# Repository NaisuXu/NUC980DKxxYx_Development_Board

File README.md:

# NUC980DKxxYx_Development_Board

## Introduction

This is a development board project for Nuvoton NUC980 Series. It can be used for LQFP128 package chips such as NUC980DK61YC, NUC980DK71YC.

This project is designed with [Kicad](https://www.kicad.org/).

## 3D Views

## What is the NUC980

> The NUC980 series with the ARM926EJ-S core can operate at up to 300 MHz . It offers 64-pin, 128-pin and 216-pin LQFP packages stacked with 64 MB and 128 MB DDR-II Memory to reduce PCB size and EMI issues. Rich peripherals include 10 sets of UART , dual Ethernet, 4 sets CAN 2.0B, dual SDIO / eMMC interface, NAND Flash interface, QSPI NAND, 8 Ports USB Host, ISO-7816 interface and High-Speed USB 2.0 host / device controller to allow more flexibility in designs. The NUC980 also integrates the crypto engine which provides hardware acceleration for AES, SHA, ECC, RSA  function.
>
> It supports industrial temperature from - 40 ℃  to 85 ℃  and targets Industrial Control, Industrial IoT Gateway, Network Printer, Meter Concentrator and Smart Home Gateway applications.

For more details see the Nuvoton website: [NUC980 工业控制物联网系列](https://www.nuvoton.com.cn/products/microprocessors/arm9-mpus/nuc980-industrial-control-iot-series/)

## License
<br />This work is licensed under a <a rel="license" href="http://creativecommons.org/licenses/by-sa/4.0/">Creative Commons Attribution-ShareAlike 4.0 International License</a>.

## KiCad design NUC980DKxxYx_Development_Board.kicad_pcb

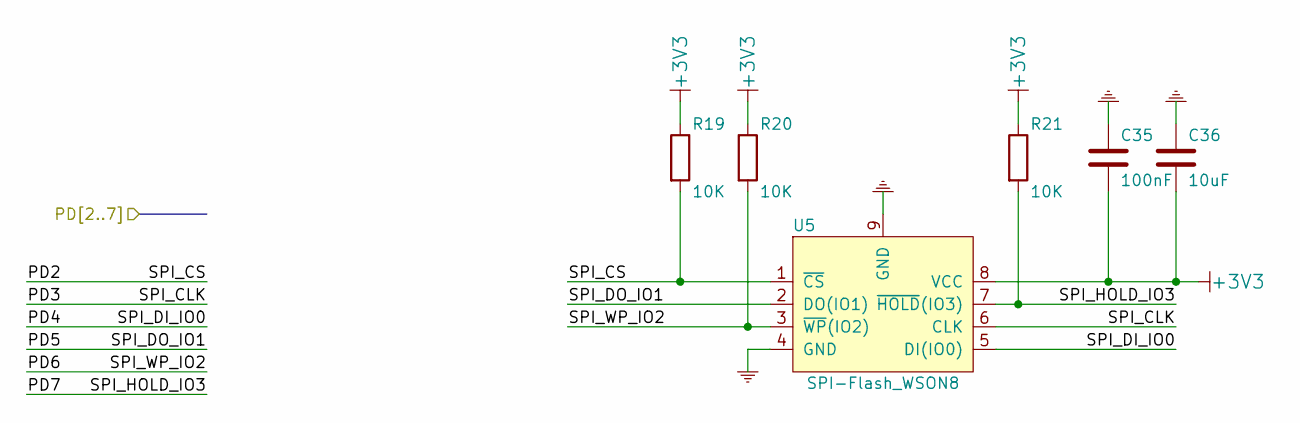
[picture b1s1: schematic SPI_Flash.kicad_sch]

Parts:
C35: 100nF; C_0603_1608Metric
C36: 10uF; C_0805_2012Metric
R19, R20, R21: 10K; R_0603_1608Metric
U5: SPI-Flash_WSON8; WSON-8-1EP_8x6mm_P1.27mm_EP3.4x4.3mm

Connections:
+3V3: C35.2, C36.2, R19.1, R20.1, R21.1, U5.8 (VCC); also elsewhere on the board
/PD2: R19.2, U5.1 (~CS); also elsewhere on the board
/PD3: U5.6 (CLK); also elsewhere on the board
/PD4: U5.5 (DI(IO0)); also elsewhere on the board
/PD5: U5.2 (DO(IO1)); also elsewhere on the board
/PD6: R20.2, U5.3 (~WP(IO2)); also elsewhere on the board
/PD7: R21.2, U5.7 (~HOLD(IO3)); also elsewhere on the board
GND: C35.1, C36.1, U5.4 (GND), U5.9 (GND); also elsewhere on the board

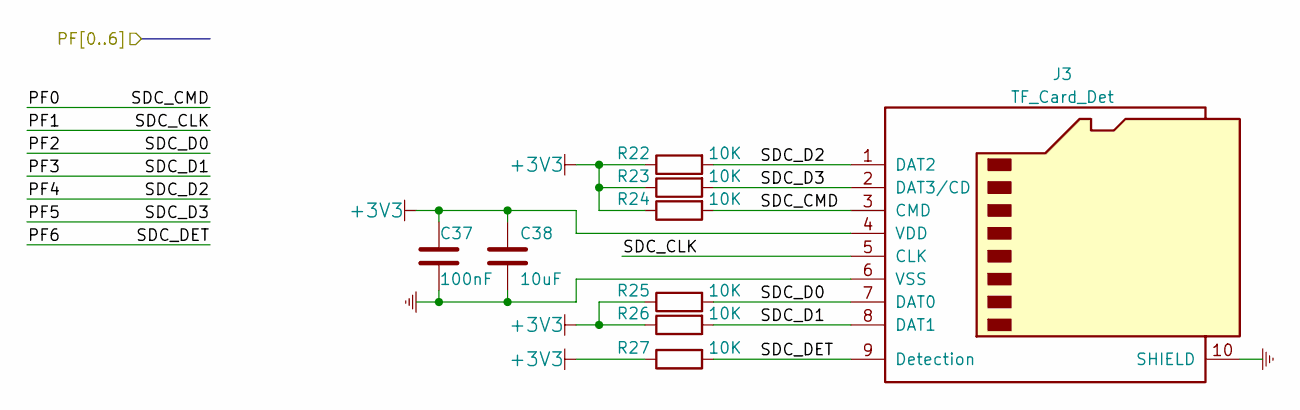
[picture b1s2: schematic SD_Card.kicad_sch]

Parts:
C37: 100nF; C_0603_1608Metric
C38: 10uF; C_0805_2012Metric
J3: TF_Card_Det; microSD_Push-Push_9P_4Pad
R22, R23, R24, R25, R26, R27: 10K; R_0603_1608Metric

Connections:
+3V3: C37.1, C38.1, J3.4 (VDD), R22.1, R23.1, R24.1, R25.1, R26.1, R27.1; also elsewhere on the board
/PF0: J3.3 (CMD), R24.2; also elsewhere on the board
/PF1: J3.5 (CLK); also elsewhere on the board
/PF2: J3.7 (DAT0), R25.2; also elsewhere on the board
/PF3: J3.8 (DAT1), R26.2; also elsewhere on the board
/PF4: J3.1 (DAT2), R22.2; also elsewhere on the board
/PF5: J3.2 (DAT3/CD), R23.2; also elsewhere on the board
/PF6: J3.9 (Detection), R27.2; also elsewhere on the board
GND: C37.2, C38.2, J3.6 (VSS), J3.10 (SHIELD); also elsewhere on the board

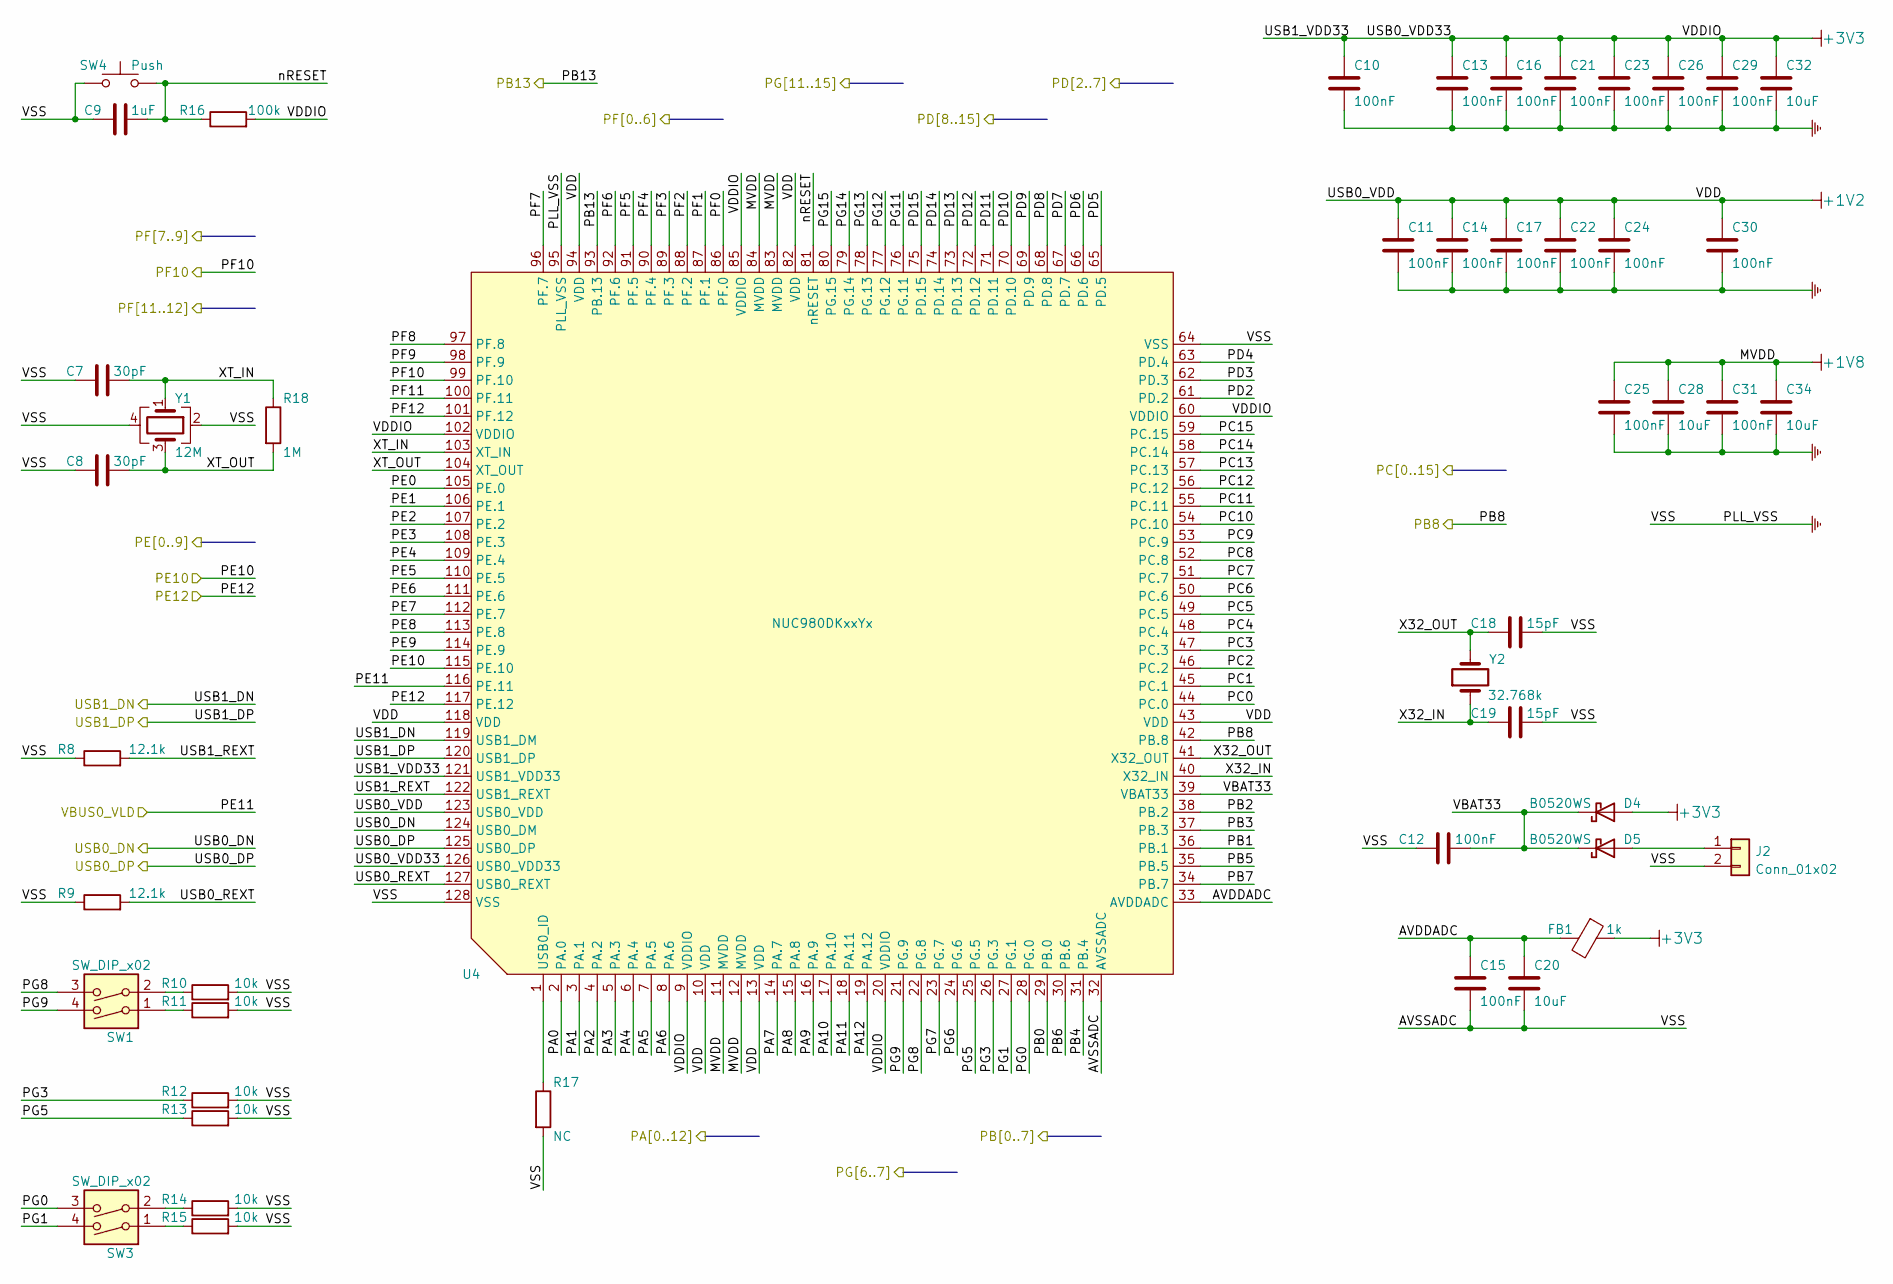
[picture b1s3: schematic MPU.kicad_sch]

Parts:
C7, C8: 30pF; C_0603_1608Metric
C9: 1uF; C_0603_1608Metric
C10, C11, C12, C13, C14, C15, C16, C17, C21, C22, C23, C24, C25, C26, C29, C30, C31: 100nF; C_0603_1608Metric
C18, C19: 15pF; C_0603_1608Metric
C20, C28, C32, C34: 10uF; C_0805_2012Metric
D4, D5: B0520WS; D_SOD-323
FB1: 1k; L_0603_1608Metric
J2: Conn_01x02; PinHeader_1x02_P2.54mm_Vertical
R8, R9: 12.1k; R_0603_1608Metric
R10, R11, R12, R13, R14, R15: 10k; R_0603_1608Metric
R16: 100k; R_0603_1608Metric
R17: NC; R_0603_1608Metric
R18: 1M; R_0603_1608Metric
SW1, SW3: SW_DIP_x02; SW_DIP_SPSTx02_Slide_9.78x7.26mm_W7.62mm_P2.54mm
SW4: Push; SW_SPST_CK_RS282G05A3
U4: NUC980DKxxYx; LQFP-128_14x14mm_P0.4mm
Y1: 12M; Crystal_SMD_3225-4Pin_3.2x2.5mm
Y2: 32.768k; Crystal_SMD_3215-2Pin_3.2x1.5mm

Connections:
+1V2: C11.1, C14.1, C17.1, C22.1, C24.1, C30.1, U4.10 (VDD), U4.13 (VDD), U4.43 (VDD), U4.82 (VDD), U4.94 (VDD), U4.118 (VDD), U4.123 (USB0_VDD); also elsewhere on the board
+1V8: C25.1, C28.1, C31.1, C34.1, U4.11 (MVDD), U4.12 (MVDD), U4.83 (MVDD), U4.84 (MVDD); also elsewhere on the board
+3V3: C10.1, C13.1, C16.1, C21.1, C23.1, C26.1, C29.1, C32.1, D4.2 (A), FB1.1, R16.2, U4.9 (VDDIO), U4.20 (VDDIO), U4.60 (VDDIO), U4.85 (VDDIO), U4.102 (VDDIO), U4.121 (USB1_VDD33), U4.126 (USB0_VDD33); also elsewhere on the board
/MPU/AVDDADC: C15.1, C20.1, FB1.2, U4.33 (AVDDADC)
/MPU/PG0: SW3.3, U4.28 (PG.0)
/MPU/PG1: SW3.4, U4.27 (PG.1)
/MPU/PG3: R12.1, U4.26 (PG.3)
/MPU/PG5: R13.1, U4.25 (PG.5)
/MPU/PG8: SW1.3, U4.22 (PG.8)
/MPU/PG9: SW1.4, U4.21 (PG.9)
/MPU/USB0_REXT: R9.2, U4.127 (USB0_REXT)
/MPU/USB1_REXT: R8.2, U4.122 (USB1_REXT)
/MPU/VBAT33: C12.2, D4.1 (K), D5.1 (K), U4.39 (VBAT33)
/MPU/X32_IN: C19.1, U4.40 (X32_IN), Y2.1
/MPU/X32_OUT: C18.1, U4.41 (X32_OUT), Y2.2
/MPU/XT_IN: C7.2, R18.1, U4.103 (XT_IN), Y1.1
/MPU/XT_OUT: C8.2, R18.2, U4.104 (XT_OUT), Y1.3
/MPU/nRESET: C9.2, R16.1, SW4.1, U4.81 (nRESET)
/PA0: U4.2 (PA.0); also elsewhere on the board
/PA1: U4.3 (PA.1); also elsewhere on the board
/PA2: U4.4 (PA.2); also elsewhere on the board
/PA3: U4.5 (PA.3); also elsewhere on the board
/PA4: U4.6 (PA.4); also elsewhere on the board
/PA5: U4.7 (PA.5); also elsewhere on the board
/PA6: U4.8 (PA.6); also elsewhere on the board
/PA7: U4.14 (PA.7); also elsewhere on the board
/PA8: U4.15 (PA.8); also elsewhere on the board
/PA9: U4.16 (PA.9); also elsewhere on the board
/PA10: U4.17 (PA.10); also elsewhere on the board
/PA11: U4.18 (PA.11); also elsewhere on the board
/PA12: U4.19 (PA.12); also elsewhere on the board
/PB0: U4.29 (PB.0); also elsewhere on the board
/PB1: U4.36 (PB.1); also elsewhere on the board
/PB2: U4.38 (PB.2); also elsewhere on the board
/PB3: U4.37 (PB.3); also elsewhere on the board
/PB4: U4.31 (PB.4); also elsewhere on the board
/PB5: U4.35 (PB.5); also elsewhere on the board
/PB6: U4.30 (PB.6); also elsewhere on the board
/PB7: U4.34 (PB.7); also elsewhere on the board
/PB8: U4.42 (PB.8); also elsewhere on the board
/PB13: U4.93 (PB.13); also elsewhere on the board
/PC0: U4.44 (PC.0); also elsewhere on the board
/PC1: U4.45 (PC.1); also elsewhere on the board
/PC2: U4.46 (PC.2); also elsewhere on the board
/PC3: U4.47 (PC.3); also elsewhere on the board
/PC4: U4.48 (PC.4); also elsewhere on the board
/PC5: U4.49 (PC.5); also elsewhere on the board
/PC6: U4.50 (PC.6); also elsewhere on the board
/PC7: U4.51 (PC.7); also elsewhere on the board
/PC8: U4.52 (PC.8); also elsewhere on the board
/PC9: U4.53 (PC.9); also elsewhere on the board
/PC10: U4.54 (PC.10); also elsewhere on the board
/PC11: U4.55 (PC.11); also elsewhere on the board
/PC12: U4.56 (PC.12); also elsewhere on the board
/PC13: U4.57 (PC.13); also elsewhere on the board
/PC14: U4.58 (PC.14); also elsewhere on the board
/PC15: U4.59 (PC.15); also elsewhere on the board
/PD2: U4.61 (PD.2); also elsewhere on the board
/PD3: U4.62 (PD.3); also elsewhere on the board
/PD4: U4.63 (PD.4); also elsewhere on the board
/PD5: U4.65 (PD.5); also elsewhere on the board
/PD6: U4.66 (PD.6); also elsewhere on the board
/PD7: U4.67 (PD.7); also elsewhere on the board
/PD8: U4.68 (PD.8); also elsewhere on the board
/PD9: U4.69 (PD.9); also elsewhere on the board
/PD10: U4.70 (PD.10); also elsewhere on the board
/PD11: U4.71 (PD.11); also elsewhere on the board
/PD12: U4.72 (PD.12); also elsewhere on the board
/PD13: U4.73 (PD.13); also elsewhere on the board
/PD14: U4.74 (PD.14); also elsewhere on the board
/PD15: U4.75 (PD.15); also elsewhere on the board
/PE0: U4.105 (PE.0); also elsewhere on the board
/PE1: U4.106 (PE.1); also elsewhere on the board
/PE2: U4.107 (PE.2); also elsewhere on the board
/PE3: U4.108 (PE.3); also elsewhere on the board
/PE4: U4.109 (PE.4); also elsewhere on the board
/PE5: U4.110 (PE.5); also elsewhere on the board
/PE6: U4.111 (PE.6); also elsewhere on the board
/PE7: U4.112 (PE.7); also elsewhere on the board
/PE8: U4.113 (PE.8); also elsewhere on the board
/PE9: U4.114 (PE.9); also elsewhere on the board
/PE10: U4.115 (PE.10); also elsewhere on the board
/PE12: U4.117 (PE.12); also elsewhere on the board
/PF0: U4.86 (PF.0); also elsewhere on the board
/PF1: U4.87 (PF.1); also elsewhere on the board
/PF2: U4.88 (PF.2); also elsewhere on the board
/PF3: U4.89 (PF.3); also elsewhere on the board
/PF4: U4.90 (PF.4); also elsewhere on the board
/PF5: U4.91 (PF.5); also elsewhere on the board
/PF6: U4.92 (PF.6); also elsewhere on the board
/PF7: U4.96 (PF.7); also elsewhere on the board
/PF8: U4.97 (PF.8); also elsewhere on the board
/PF9: U4.98 (PF.9); also elsewhere on the board
/PF10: U4.99 (PF.10); also elsewhere on the board
/PF11: U4.100 (PF.11); also elsewhere on the board
/PF12: U4.101 (PF.12); also elsewhere on the board
/PG6: U4.24 (PG.6); also elsewhere on the board
/PG7: U4.23 (PG.7); also elsewhere on the board
/PG11: U4.76 (PG.11); also elsewhere on the board
/PG12: U4.77 (PG.12); also elsewhere on the board
/PG13: U4.78 (PG.13); also elsewhere on the board
/PG14: U4.79 (PG.14); also elsewhere on the board
/PG15: U4.80 (PG.15); also elsewhere on the board
/USB0_DN: U4.124 (USB0_DM); also elsewhere on the board
/USB0_DP: U4.125 (USB0_DP); also elsewhere on the board
/USB1_DN: U4.119 (USB1_DM); also elsewhere on the board
/USB1_DP: U4.120 (USB1_DP); also elsewhere on the board
/VBUS0_VLD: U4.116 (PE.11); also elsewhere on the board
GND: C7.1, C8.1, C9.1, C10.2, C11.2, C12.1, C13.2, C14.2, C15.2, C16.2, C17.2, C18.2, C19.2, C20.2, C21.2, C22.2, C23.2, C24.2, C25.2, C26.2, C28.2, C29.2, C30.2, C31.2, C32.2, C34.2, J2.2, R8.1, R9.1, R10.2, R11.2, R12.2, R13.2, R14.2, R15.2, R17.2, SW4.2, U4.32 (AVSSADC), U4.64 (VSS), U4.95 (PLL_VSS), U4.128 (VSS), Y1.2, Y1.4; also elsewhere on the board
unnamed: D5.2 (A), J2.1
unnamed: R10.1, SW1.2
unnamed: R11.1, SW1.1
unnamed: R14.1, SW3.2
unnamed: R15.1, SW3.1
unnamed: R17.1, U4.1 (USB0_ID)

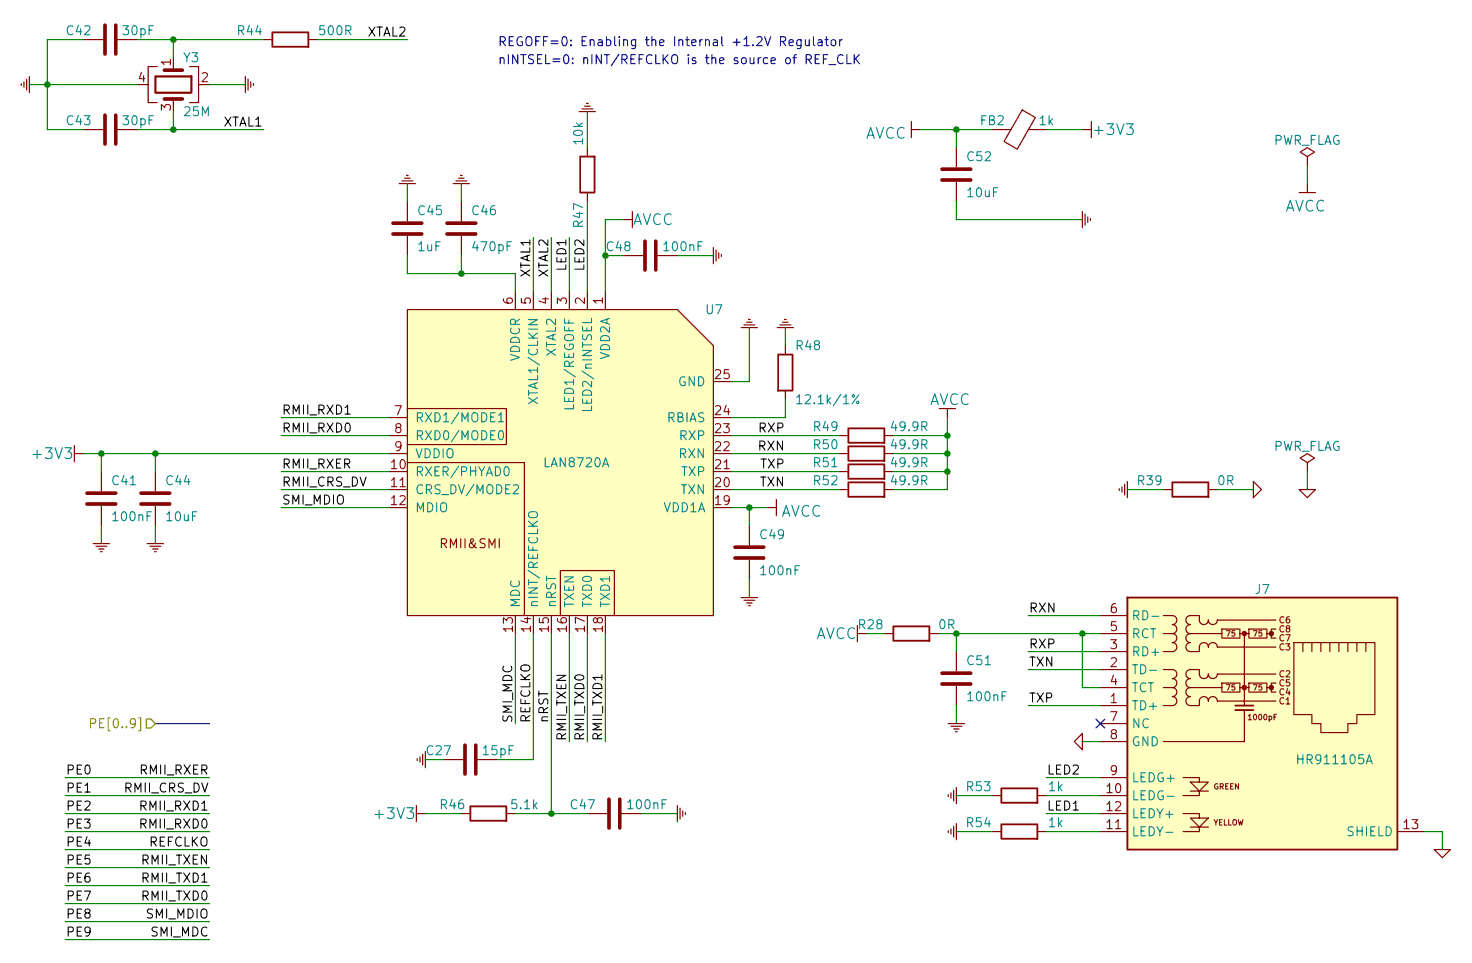
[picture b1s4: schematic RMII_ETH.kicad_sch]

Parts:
C27: 15pF; C_0603_1608Metric
C41, C47, C48, C49, C51: 100nF; C_0603_1608Metric
C42, C43: 30pF; C_0603_1608Metric
C44, C52: 10uF; C_0805_2012Metric
C45: 1uF; C_0603_1608Metric
C46: 470pF; C_0603_1608Metric
FB2: 1k; L_0603_1608Metric
J7: HR911105A
R28, R39: 0R; R_0603_1608Metric
R44: 500R; R_0603_1608Metric
R46: 5.1k; R_0603_1608Metric
R47: 10k; R_0603_1608Metric
R48: 12.1k/1%; R_0603_1608Metric
R49, R50, R51, R52: 49.9R; R_0603_1608Metric
R53, R54: 1k; R_0603_1608Metric
U7: LAN8720A; QFN-24-1EP_4x4mm_P0.5mm_EP2.4x2.4mm
Y3: 25M; Crystal_SMD_3225-4Pin_3.2x2.5mm

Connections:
+3V3: C41.1, C44.1, FB2.1, R46.1, U7.9 (VDDIO); also elsewhere on the board
/PE0: U7.10 (RXER/PHYAD0); also elsewhere on the board
/PE1: U7.11 (CRS_DV/MODE2); also elsewhere on the board
/PE2: U7.7 (RXD1/MODE1); also elsewhere on the board
/PE3: U7.8 (RXD0/MODE0); also elsewhere on the board
/PE4: C27.2, U7.14 (nINT/REFCLKO); also elsewhere on the board
/PE5: U7.16 (TXEN); also elsewhere on the board
/PE6: U7.18 (TXD1); also elsewhere on the board
/PE7: U7.17 (TXD0); also elsewhere on the board
/PE8: U7.12 (MDIO); also elsewhere on the board
/PE9: U7.13 (MDC); also elsewhere on the board
/RMII_ETH/LED1: J7.12 (LEDY+), U7.3 (LED1/REGOFF)
/RMII_ETH/LED2: J7.9 (LEDG+), R47.1, U7.2 (LED2/nINTSEL)
/RMII_ETH/RXN: J7.6 (RD-), R50.1, U7.22 (RXN)
/RMII_ETH/RXP: J7.3 (RD+), R49.1, U7.23 (RXP)
/RMII_ETH/TXN: J7.2 (TD-), R52.1, U7.20 (TXN)
/RMII_ETH/TXP: J7.1 (TD+), R51.1, U7.21 (TXP)
/RMII_ETH/XTAL1: C43.2, U7.5 (XTAL1/CLKIN), Y3.3
/RMII_ETH/XTAL2: R44.2, U7.4 (XTAL2)
/RMII_ETH/nRST: C47.1, R46.2, U7.15 (nRST)
GND: C27.1, C41.2, C42.1, C43.1, C44.2, C45.1, C46.1, C47.2, C48.2, C49.2, C51.2, C52.2, R39.1, R47.2, R48.1, R53.1, R54.1, U7.25 (GND), Y3.2, Y3.4; also elsewhere on the board
GNDA: J7.8 (GND), J7.13 (SHIELD), R39.2
unnamed: C42.2, R44.1, Y3.1
unnamed: C45.2, C46.2, U7.6 (VDDCR)
unnamed: C51.1, J7.4 (TCT), J7.5 (RCT), R28.2
unnamed: J7.10 (LEDG-), R53.2
unnamed: J7.11 (LEDY-), R54.2
unnamed: R48.2, U7.24 (RBIAS)
VCC: C48.1, C49.1, C52.1, FB2.2, R28.1, R49.2, R50.2, R51.2, R52.2, U7.1 (VDD2A), U7.19 (VDD1A)

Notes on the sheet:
REGOFF=0: Enabling the Internal +1.2V Regulator
nINTSEL=0: nINT/REFCLKO is the source of REF_CLK

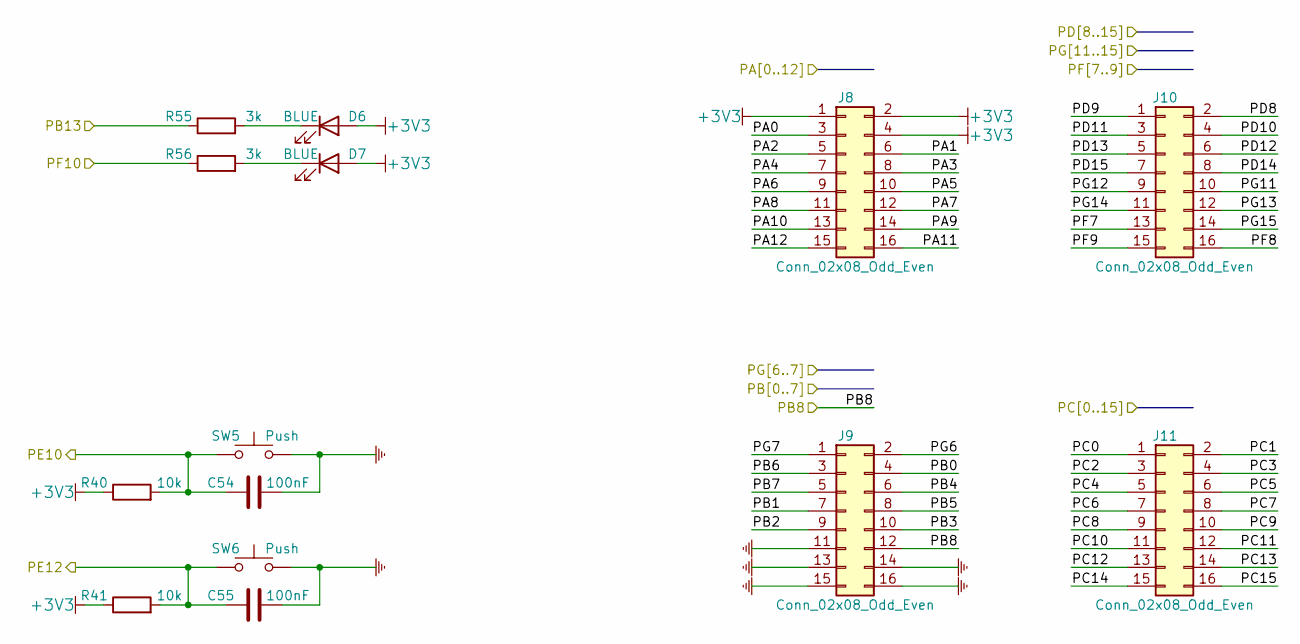
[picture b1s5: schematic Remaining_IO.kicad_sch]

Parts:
C54, C55: 100nF; C_0603_1608Metric
D6, D7: BLUE; LED_0603_1608Metric
J8, J9, J10, J11: Conn_02x08_Odd_Even; PinHeader_2x08_P2.54mm_Vertical
R40, R41: 10k; R_0603_1608Metric
R55, R56: 3k; R_0603_1608Metric
SW5, SW6: Push; SW_SPST_CK_RS282G05A3

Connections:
+3V3: D6.2 (A), D7.2 (A), J8.1, J8.2, J8.4, R40.1, R41.1; also elsewhere on the board
/PA0: J8.3; also elsewhere on the board
/PA1: J8.6; also elsewhere on the board
/PA2: J8.5; also elsewhere on the board
/PA3: J8.8; also elsewhere on the board
/PA4: J8.7; also elsewhere on the board
/PA5: J8.10; also elsewhere on the board
/PA6: J8.9; also elsewhere on the board
/PA7: J8.12; also elsewhere on the board
/PA8: J8.11; also elsewhere on the board
/PA9: J8.14; also elsewhere on the board
/PA10: J8.13; also elsewhere on the board
/PA11: J8.16; also elsewhere on the board
/PA12: J8.15; also elsewhere on the board
/PB0: J9.4; also elsewhere on the board
/PB1: J9.7; also elsewhere on the board
/PB2: J9.9; also elsewhere on the board
/PB3: J9.10; also elsewhere on the board
/PB4: J9.6; also elsewhere on the board
/PB5: J9.8; also elsewhere on the board
/PB6: J9.3; also elsewhere on the board
/PB7: J9.5; also elsewhere on the board
/PB8: J9.12; also elsewhere on the board
/PB13: R55.1; also elsewhere on the board
/PC0: J11.1; also elsewhere on the board
/PC1: J11.2; also elsewhere on the board
/PC2: J11.3; also elsewhere on the board
/PC3: J11.4; also elsewhere on the board
/PC4: J11.5; also elsewhere on the board
/PC5: J11.6; also elsewhere on the board
/PC6: J11.7; also elsewhere on the board
/PC7: J11.8; also elsewhere on the board
/PC8: J11.9; also elsewhere on the board
/PC9: J11.10; also elsewhere on the board
/PC10: J11.11; also elsewhere on the board
/PC11: J11.12; also elsewhere on the board
/PC12: J11.13; also elsewhere on the board
/PC13: J11.14; also elsewhere on the board
/PC14: J11.15; also elsewhere on the board
/PC15: J11.16; also elsewhere on the board
/PD8: J10.2; also elsewhere on the board
/PD9: J10.1; also elsewhere on the board
/PD10: J10.4; also elsewhere on the board
/PD11: J10.3; also elsewhere on the board
/PD12: J10.6; also elsewhere on the board
/PD13: J10.5; also elsewhere on the board
/PD14: J10.8; also elsewhere on the board
/PD15: J10.7; also elsewhere on the board
/PE10: C54.1, R40.2, SW5.2; also elsewhere on the board
/PE12: C55.1, R41.2, SW6.2; also elsewhere on the board
/PF7: J10.13; also elsewhere on the board
/PF8: J10.16; also elsewhere on the board
/PF9: J10.15; also elsewhere on the board
/PF10: R56.1; also elsewhere on the board
/PG6: J9.2; also elsewhere on the board
/PG7: J9.1; also elsewhere on the board
/PG11: J10.10; also elsewhere on the board
/PG12: J10.9; also elsewhere on the board
/PG13: J10.12; also elsewhere on the board
/PG14: J10.11; also elsewhere on the board
/PG15: J10.14; also elsewhere on the board
GND: C54.2, C55.2, J9.11, J9.13, J9.14, J9.15, J9.16, SW5.1, SW6.1; also elsewhere on the board
unnamed: D6.1 (K), R55.2
unnamed: D7.1 (K), R56.2

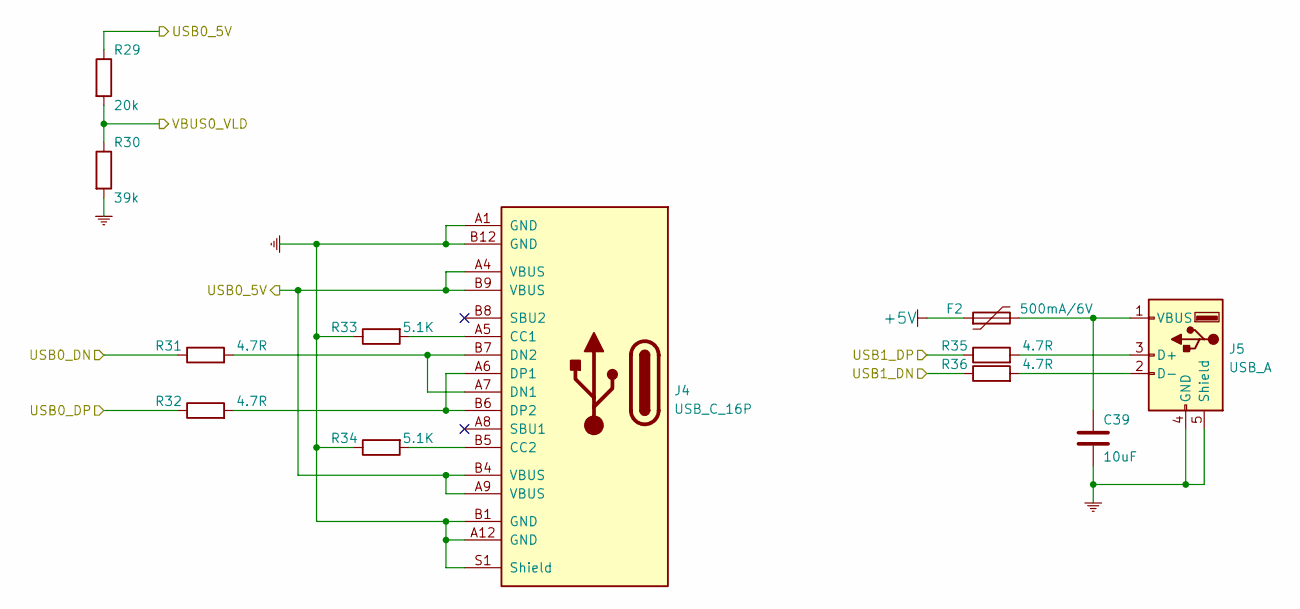
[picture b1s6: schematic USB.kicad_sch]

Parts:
C39: 10uF; C_0805_2012Metric
F2: 500mA/6V; Fuse_1206_3216Metric_Pad1.42x1.75mm_HandSolder
J4: USB_C_16P; USB_C_16P_4Foot8.64mm
J5: USB_A; USB_A_90Deg_THT_Horizontal
R29: 20k; R_0603_1608Metric
R30: 39k; R_0603_1608Metric
R31, R32, R35, R36: 4.7R; R_0603_1608Metric
R33, R34: 5.1K; R_0603_1608Metric

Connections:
+5V: F2.1; also elsewhere on the board
/USB0_5V: J4.A4 (VBUS), J4.A9 (VBUS), J4.B4 (VBUS), J4.B9 (VBUS), R29.1; also elsewhere on the board
/USB0_DN: R31.1; also elsewhere on the board
/USB0_DP: R32.1; also elsewhere on the board
/USB1_DN: R36.1; also elsewhere on the board
/USB1_DP: R35.1; also elsewhere on the board
/VBUS0_VLD: R29.2, R30.1; also elsewhere on the board
GND: C39.2, J4.A1 (GND), J4.A12 (GND), J4.B1 (GND), J4.B12 (GND), J4.S1 (Shield), J5.4 (GND), J5.5 (Shield), R30.2, R33.1, R34.1; also elsewhere on the board
unnamed: C39.1, F2.2, J5.1 (VBUS)
unnamed: J4.A5 (CC1), R33.2
unnamed: J4.A6 (DP1), J4.B6 (DP2), R32.2
unnamed: J4.A7 (DN1), J4.B7 (DN2), R31.2
unnamed: J4.B5 (CC2), R34.2
unnamed: J5.2 (D-), R36.2
unnamed: J5.3 (D+), R35.2

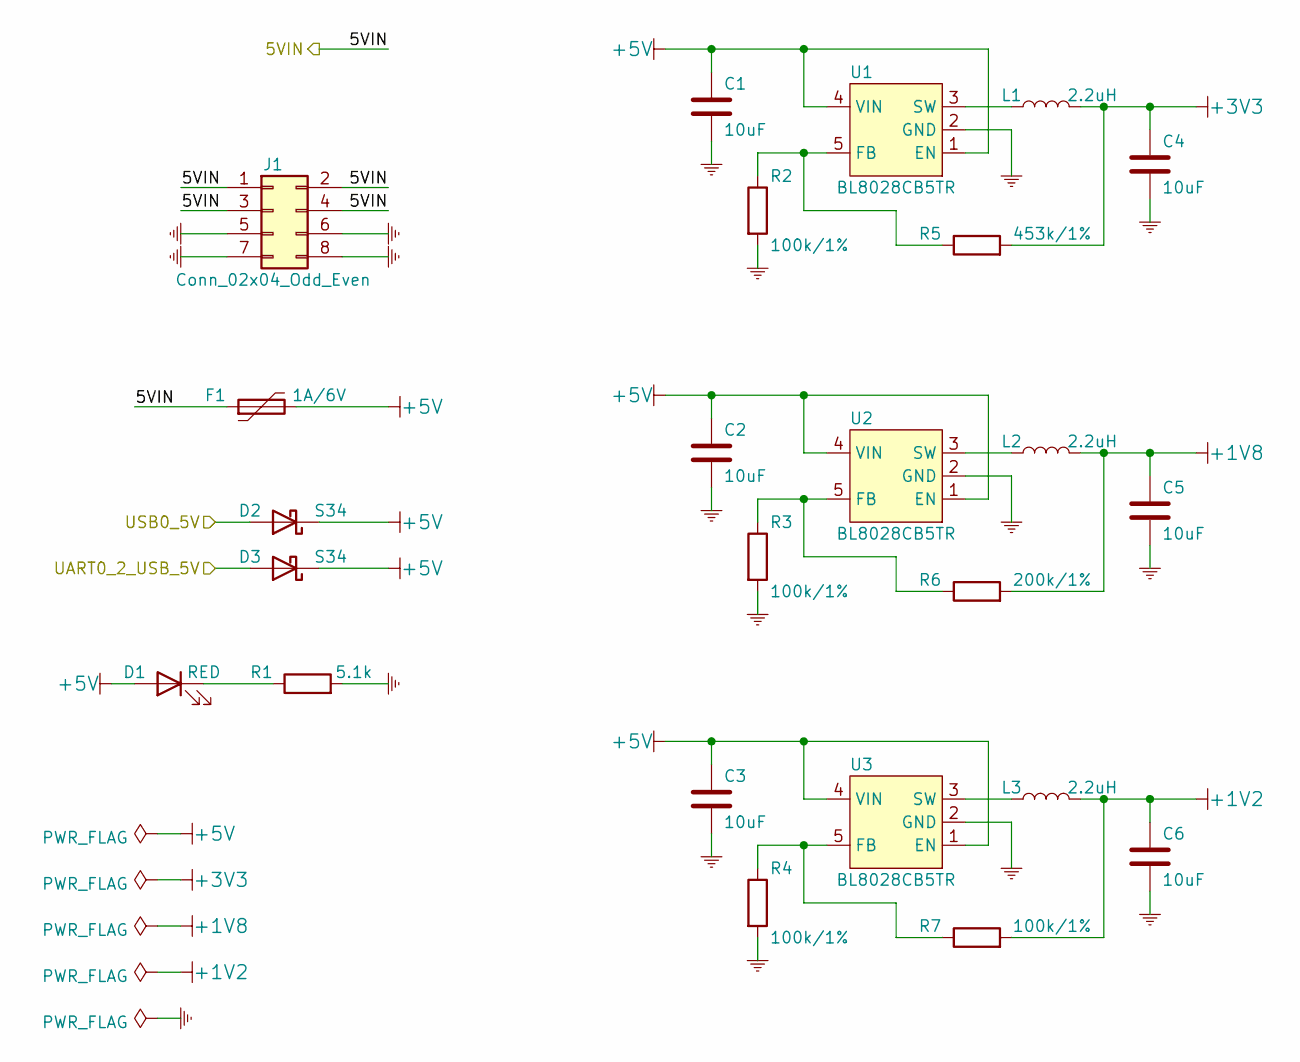
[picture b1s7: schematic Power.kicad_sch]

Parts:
C1, C2, C3, C4, C5, C6: 10uF; C_0805_2012Metric
D1: RED; LED_0603_1608Metric
D2, D3: S34; D_SOD-123F
F1: 1A/6V; Fuse_1206_3216Metric_Pad1.42x1.75mm_HandSolder
J1: Conn_02x04_Odd_Even; PinHeader_2x04_P2.54mm_Vertical
L1, L2, L3: 2.2uH; Inductor_SMD_2520_2.5x2.0mm
R1: 5.1k; R_0603_1608Metric
R2, R3, R4, R7: 100k/1%; R_0603_1608Metric
R5: 453k/1%; R_0603_1608Metric
R6: 200k/1%; R_0603_1608Metric
U1, U2, U3: BL8028CB5TR; SOT-23-5

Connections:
+1V2: C6.1, L3.2, R7.2; also elsewhere on the board
+1V8: C5.1, L2.2, R6.2; also elsewhere on the board
+3V3: C4.1, L1.2, R5.2; also elsewhere on the board
+5V: C1.1, C2.1, C3.1, D1.2 (A), D2.1 (K), D3.1 (K), F1.2, U1.1 (EN), U1.4 (VIN), U2.1 (EN), U2.4 (VIN), U3.1 (EN), U3.4 (VIN); also elsewhere on the board
/5VIN: F1.1, J1.1, J1.2, J1.3, J1.4
/UART0_2_USB_5V: D3.2 (A); also elsewhere on the board
/USB0_5V: D2.2 (A); also elsewhere on the board
GND: C1.2, C2.2, C3.2, C4.2, C5.2, C6.2, J1.5, J1.6, J1.7, J1.8, R1.2, R2.2, R3.2, R4.2, U1.2 (GND), U2.2 (GND), U3.2 (GND); also elsewhere on the board
unnamed: D1.1 (K), R1.1
unnamed: L1.1, U1.3 (SW)
unnamed: L2.1, U2.3 (SW)
unnamed: L3.1, U3.3 (SW)
unnamed: R2.1, R5.1, U1.5 (FB)
unnamed: R3.1, R6.1, U2.5 (FB)
unnamed: R4.1, R7.1, U3.5 (FB)

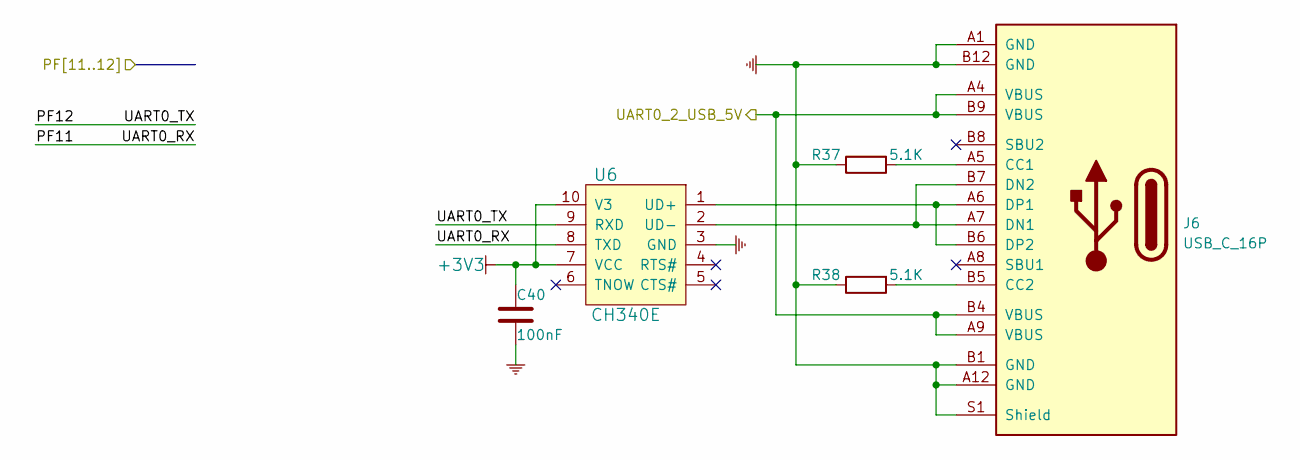
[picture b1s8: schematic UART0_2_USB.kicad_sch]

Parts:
C40: 100nF; C_0603_1608Metric
J6: USB_C_16P; USB_C_16P_4Foot8.64mm
R37, R38: 5.1K; R_0603_1608Metric
U6: CH340E; MSOP-10_3x3mm_P0.5mm

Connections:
+3V3: C40.1, U6.7 (VCC), U6.10 (V3); also elsewhere on the board
/PF11: U6.8 (TXD); also elsewhere on the board
/PF12: U6.9 (RXD); also elsewhere on the board
/UART0_2_USB_5V: J6.A4 (VBUS), J6.A9 (VBUS), J6.B4 (VBUS), J6.B9 (VBUS); also elsewhere on the board
GND: C40.2, J6.A1 (GND), J6.A12 (GND), J6.B1 (GND), J6.B12 (GND), J6.S1 (Shield), R37.1, R38.1, U6.3 (GND); also elsewhere on the board
unnamed: J6.A5 (CC1), R37.2
unnamed: J6.A6 (DP1), J6.B6 (DP2), U6.1 (UD+)
unnamed: J6.A7 (DN1), J6.B7 (DN2), U6.2 (UD-)
unnamed: J6.B5 (CC2), R38.2

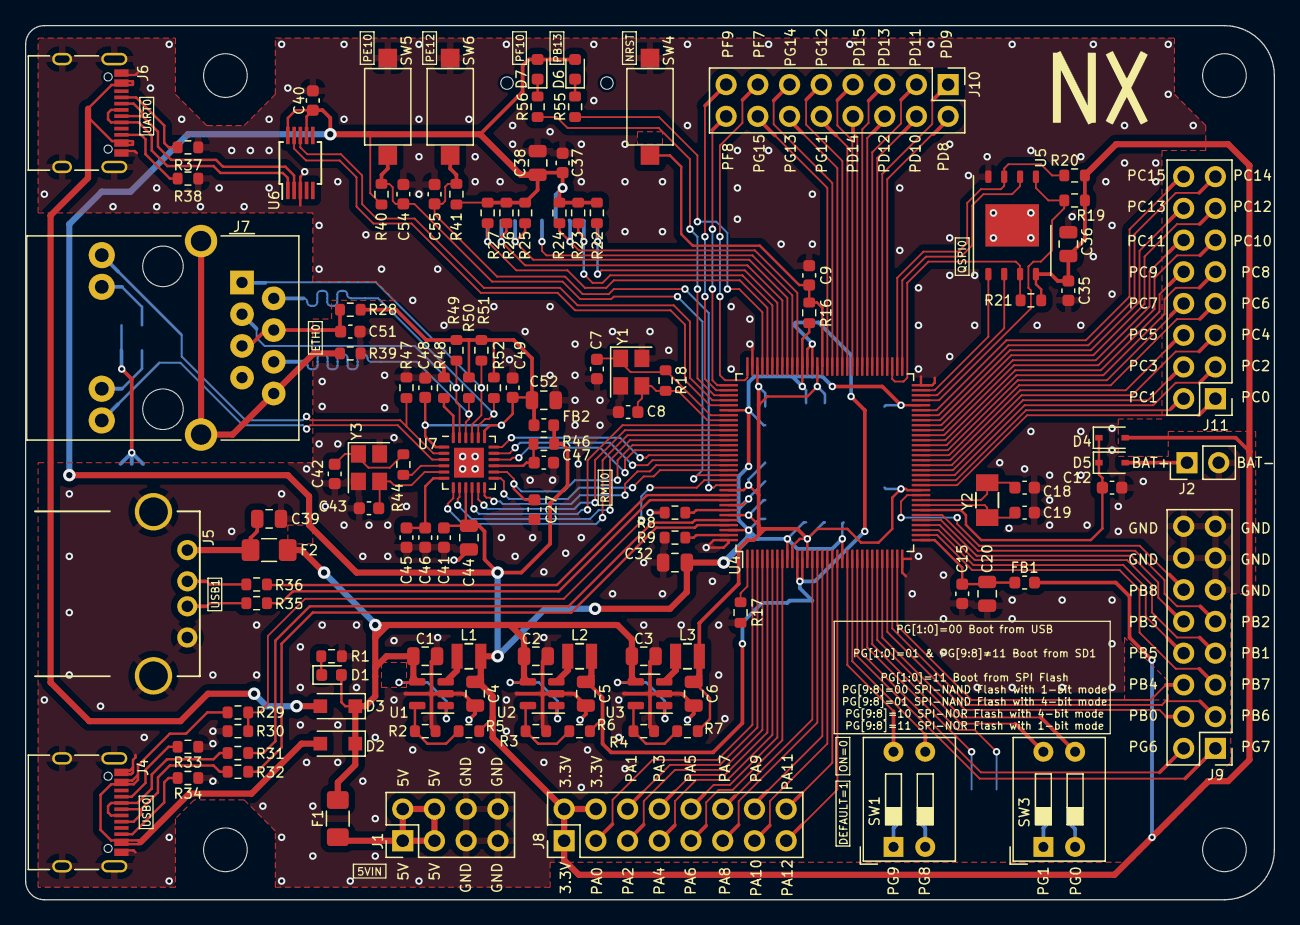
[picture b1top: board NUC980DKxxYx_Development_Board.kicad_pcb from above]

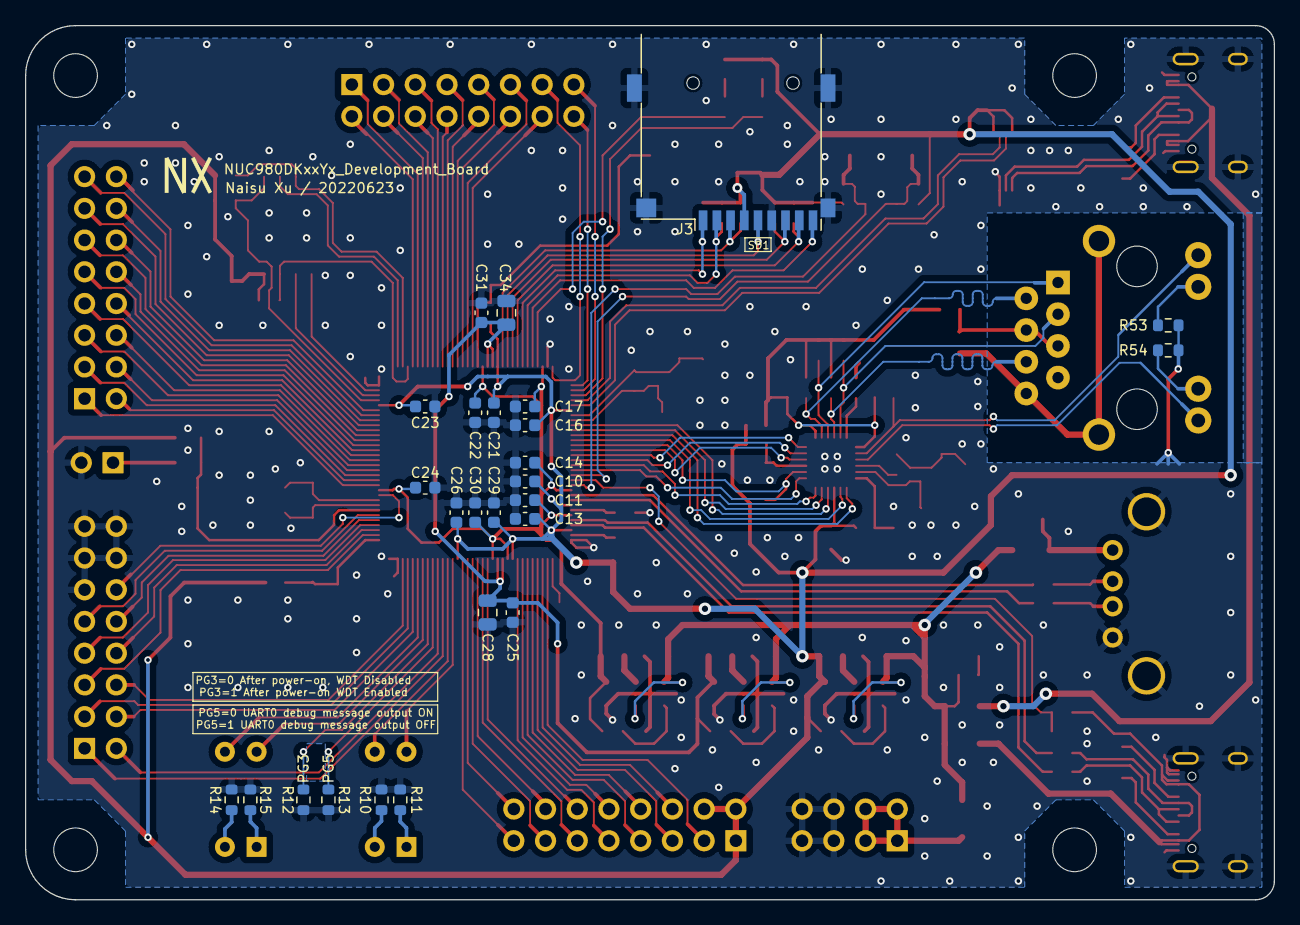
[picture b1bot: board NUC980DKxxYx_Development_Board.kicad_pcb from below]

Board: 2 copper layers, 100.0 x 70.0 mm, 145 parts (26 on the bottom side), 156 nets.

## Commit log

2022-06-27 feat: first commit.
2023-09-10 modeify: update to kicad 7.0
